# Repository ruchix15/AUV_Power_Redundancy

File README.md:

AUV_Power_Redundancy
AUV Power Redundancy Circuit (LM5050 Ideal Diode)

This is my project for the AUV electronics team task. The goal is to build a dual-input power redundancy circuit. It lets the AUV switch between two power sources (like a main battery and a backup) automatically, making sure power doesn't flow backward into the wrong source while keeping the voltage drop as low as possible.

Instead of regular diodes, I'm using an ideal diode controller setup because normal diodes drop too much voltage and waste a lot of power as heat.

What the Circuit Does
With datasheet reference , two LM5050-1 controllers (one for each power rail) driving two external N-channel MOSFETs. The controllers sense the voltage across the MOSFETs. If one supply drops or a reverse voltage happens, the chip turns off the MOSFET gate immediately to block reverse current. Both rails meet at a shared output bus that connects to the rest of the AUV systems.

Component Selection & Footprints

I chose the following parts and footprints based on our project requirements
Controller: LM5050-1 (U1, U2)
Footprint: Package_TO_SOT_SMD:SOT-23-6
This is the standard surface-mount package for this chip. It’s small enough for a compact board but still manageable to solder.

2. Pass Elements: N-Channel MOSFETs (Q1, Q2)
Footprint: Package_TO_SOT_SMD:SOT-23
Why: I selected a basic SOT-23 N-channel MOSFET for this layout. The logic behind using an N-channel FET here is that it sits on the high side with its Source on the input supply side and Drain on the output side. When the LM5050 pumps up the gate voltage, the MOSFET turns fully on, giving us an incredibly low RDS(on) (internal resistance). 

3. Passives & Connectors
Resistor & Capacitor (R1, C1): SMD:C_0805_2012Metric . I went with 0805 packages because they are the perfect for a beginner—small enough to keep the board compact, but easy enough to hand-solder without losing them with tweezers.
Connectors (J1, J2, J3):Connector_PinHeader_2.45mm:PinHeader_1x02_P2.54mm_Vertical. Standard 2-pin headers used for the power inputs and the main output.

Design Fixes I Made Along the Way
While setting up the schematic, I ran into a few issues that I had to fix:
The MOSFET Orientation: At first, the pin mappings were a bit confusing, but I fixed it so that the Source goes to the input supply and the Gate is driven safely by Pin 5 (GATE) of the LM5050.

Git Workflow
I used Git branches to make sure I didn't ruin my working schematic while fixing things.
Kept updating my changes by first running ERC and then commiting the changes to Git . 
First made the schematic , then footprint selection and then designined pcb layout by placing componenets and routing, added a gorund pad as base to overcome grounding errors .
Finally updates all changes to git and committed .

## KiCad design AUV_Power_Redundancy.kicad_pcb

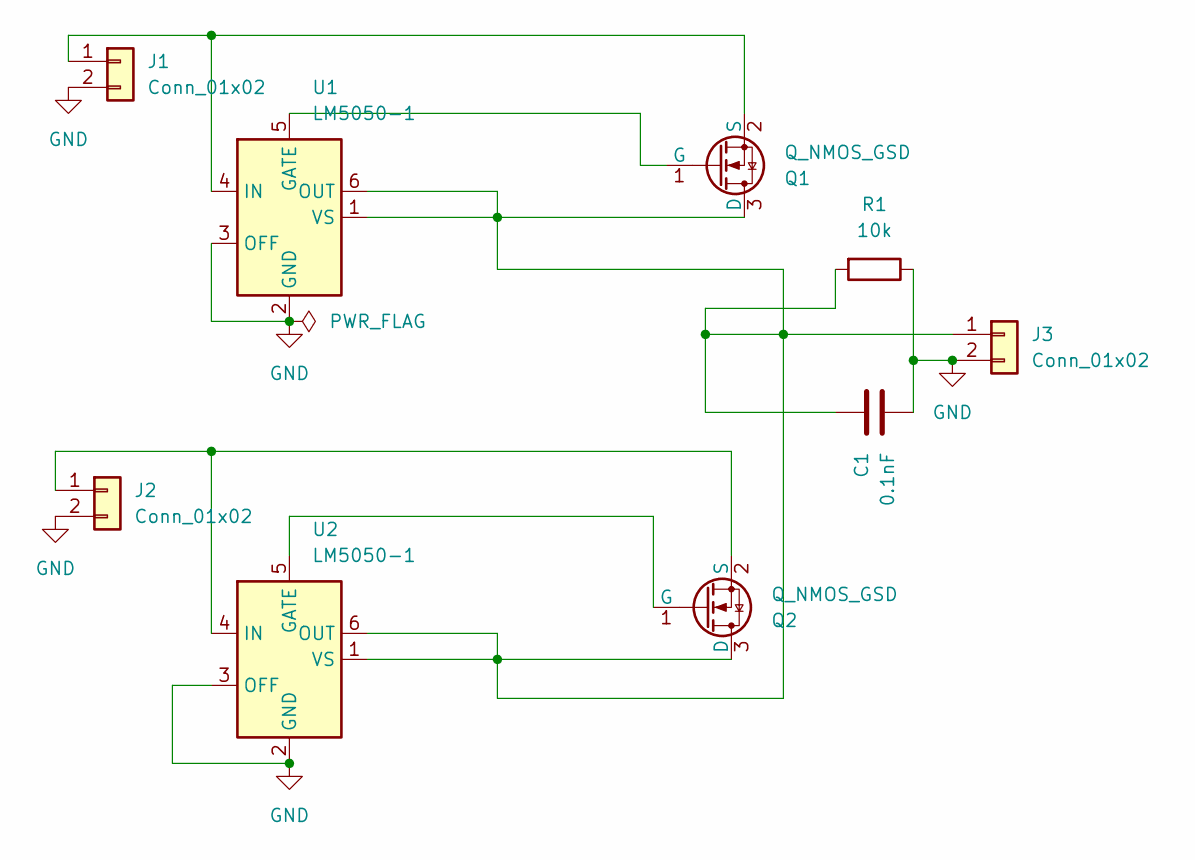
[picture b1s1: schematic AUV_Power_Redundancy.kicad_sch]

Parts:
C1: 0.1nF; C_0805_2012Metric
J1, J2, J3: Conn_01x02; PinHeader_1x02_P2.54mm_Vertical
Q1, Q2: Q_NMOS_GSD; SOT-23
R1: 10k; R_0805_2012Metric
U1, U2: LM5050-1; TSOT-23-6

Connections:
GND: C1.2, J1.2, J2.2, J3.2, R1.1, U1.2 (GND), U1.3 (OFF), U2.2 (GND), U2.3 (OFF)
unnamed: J1.1, Q1.2 (S), U1.4 (IN)
unnamed: J2.1, Q2.2 (S), U2.4 (IN)
unnamed: C1.1, J3.1, Q1.3 (D), Q2.3 (D), R1.2, U1.1 (VS), U1.6 (OUT), U2.1 (VS), U2.6 (OUT)
unnamed: Q1.1 (G), U1.5 (GATE)
unnamed: Q2.1 (G), U2.5 (GATE)

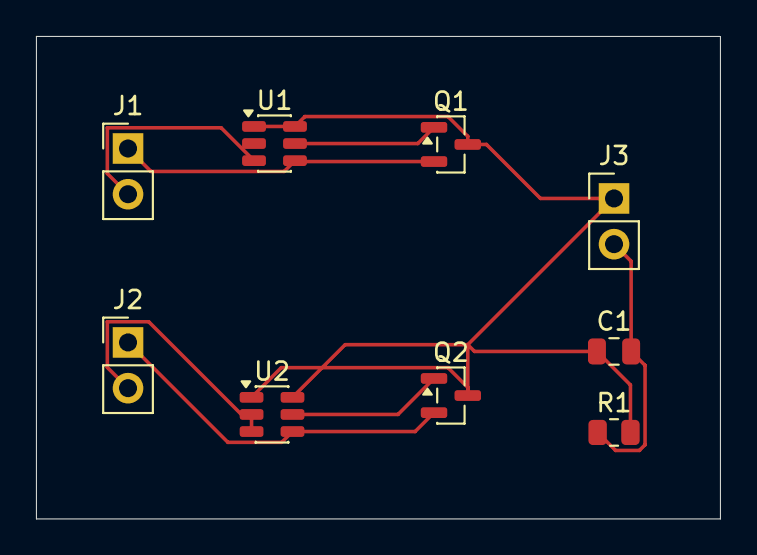
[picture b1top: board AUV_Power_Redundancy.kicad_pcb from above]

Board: 2 copper layers, 38.0 x 26.8 mm, 9 parts (0 on the bottom side), 6 nets.

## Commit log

2026-06-09 Add LM5050 redundancy circuit components
2026-06-09 Complete first LM5050 power path
2026-06-09 Complete dual LM5050 redundancy schematic
2026-06-09 Complete dual LM5050 redundancy schematic and pass ERC
2026-06-09 assigned values
2026-06-09 Assign footprints to all components
2026-06-11 pcb placement and routing completed
2026-06-28 pcb design updated
